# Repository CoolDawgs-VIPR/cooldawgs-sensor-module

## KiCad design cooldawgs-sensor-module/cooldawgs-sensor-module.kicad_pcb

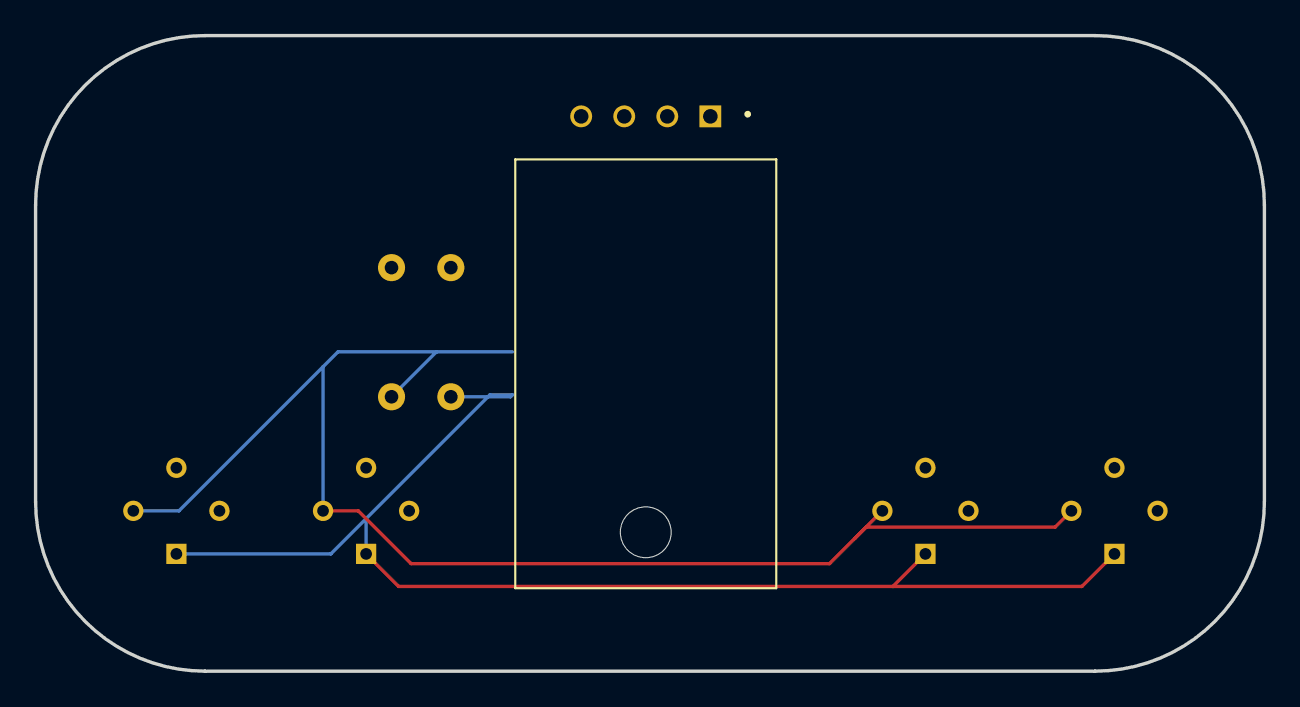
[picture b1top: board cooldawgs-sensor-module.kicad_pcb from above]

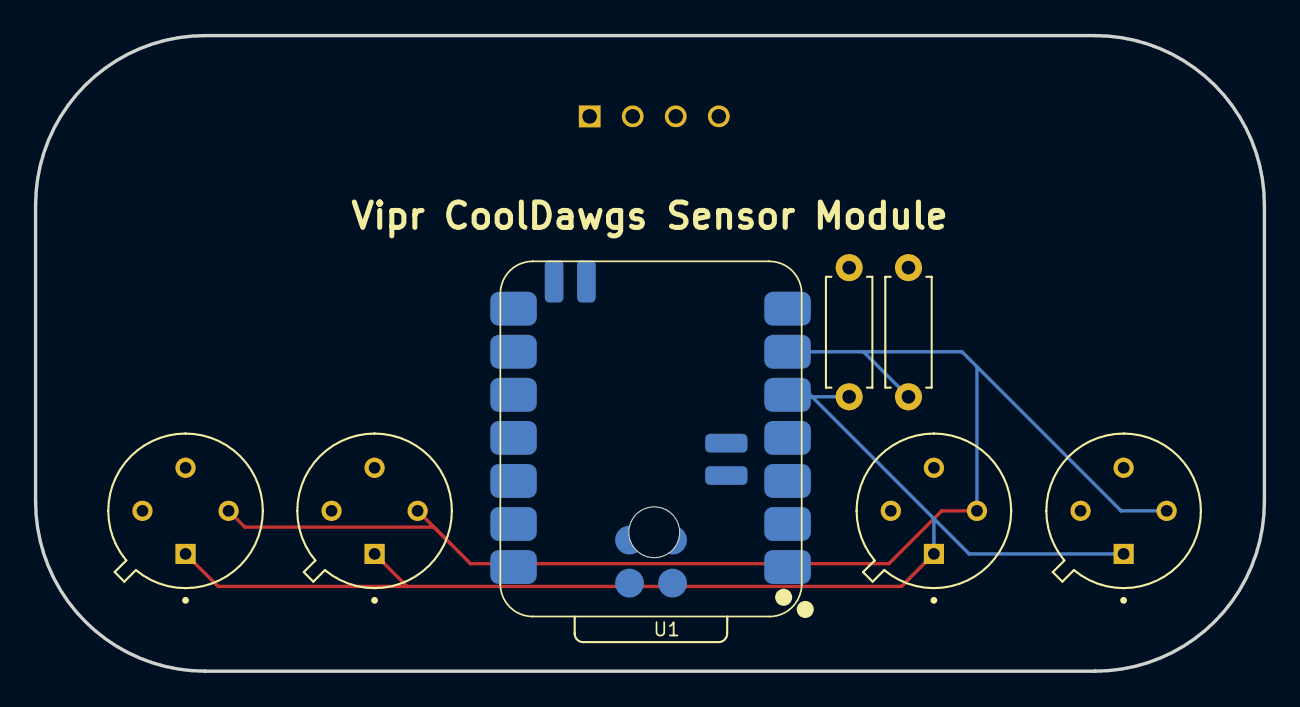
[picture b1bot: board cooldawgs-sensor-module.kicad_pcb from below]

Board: 2 copper layers, 72.5 x 37.5 mm, 8 parts (7 on the bottom side), 5 nets.

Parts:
R1, R2: R; R_Axial_DIN0207_L6.3mm_D2.5mm_P7.62mm_Horizontal
U1: XIAO-nRF52840-SMD
U2, U4, U5, U6: MLX90614ESF-AAA-000-TU; TO254P912H435-4
U3: DHT22; XDCR_DHT22

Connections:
+3.3V: R1.1, R2.1, U1.12 (3V3), U2.3 (VDD), U3.1 (VDD), U4.3 (VDD), U5.3 (VDD), U6.3 (VDD)
GND: U1.13 (GND), U2.4 (VSS), U3.4 (GND), U4.4 (VSS), U5.4 (VSS), U6.4 (VSS)
PWM: U1.2 (P0.03_A1_D1), U3.2 (DATA)
SCL: R1.2, U1.6 (P0.05_A5_D5_SCL), U2.2 (SDA/PWM), U4.2 (SDA/PWM), U5.2 (SDA/PWM), U6.2 (SDA/PWM)
SDA: R2.2, U1.5 (P0.04_A4_D4_SDA), U2.1 (SCL/VZ), U4.1 (SCL/VZ), U5.1 (SCL/VZ), U6.1 (SCL/VZ)

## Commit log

2026-02-11 added initial circuit
2026-02-11 added symbols and footprints
2026-02-11 added dht22
2026-03-19 changed files
2026-04-15 added all sensors and created initial pcb
2026-04-15 updated PCB
2026-04-15 added step 3d file of current pcb
2026-04-15 added battery from braxton
